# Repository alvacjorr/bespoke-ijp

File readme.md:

# bespoke-ijp

This repository is used for documents / code / notes related to the controller and software of the IEB bespoke inkjet printing rig. 
## Folder Structure
| Folder       |  Description  | 
| -------------| -------------|
| `/application`      | Code for the application/GUI |
| `/embedded`      | Code for the uSteppers |
| `/docs`      | Documentation |

## Workflow - Basics 
#### How do I get a copy of this repo?
- Install **Git**: https://help.github.com/en/github/getting-started-with-github/set-up-git
- Open up a terminal / command prompt and clone this repository: `git clone https://github.com/thekeeno/bespoke-ijp` which will give you a local copy of the main branch in the repository

#### Do I have to use a terminal?
- You can also use Git GUIs, e.g. https://desktop.github.com/ or https://www.gitkraken.com/

#### How do I keep my local copy updated?
- If you are on the main branch you can type `git pull`

#### How can I add / submit my changes?
- **The main main branch is protected, so you will have to create a separate branch and open a pull request.**
- The `main` branch should always reflect the newest agreed on version of the repository
- Make sure you branch off the latest state of main, i.e. on main type `git pull` or use `git fetch`
- To create a new branch use: `git checkout -b [branchname]`, e.g. `git checkout -b mg/new_branch`
- Make changes to files / add new files
- Take a look at the summary of changed files: `git status` 
- Add the new files to be tracked: `git add .` (to add all new files) or `git add code.m` (to add specific file)
- Commit the new changes (this creates a snapshot of repository state): `git commit -m "Change parameter gamma to 0.5"`
- Copy your new local branch with the new commits to the Github repository: `git push -u origin mg/new_branch`

- **Before your changes can be merged:** Make sure that you integrate the changes on `main` that others might have added in the meantime. This can be achieved by pulling the `main` changes to yout machine and then *merging* or preferably *rebasing* your commits onto the latest `main` version. See [here](https://gist.github.com/blackfalcon/8428401#keeping-current-with-the-master-branch) for a more detailed explanation.
- On https://github.com/oxfordcontrol/OxVentControl/ click on `Pull requests` -> `New Pull Request`. 
- Select `base:main` and `compare:mg/new_branch`
- All the changes can then be discussed in that pull request before they are approved and added to the main branch.
#### Useful git commands:
- https://rogerdudler.github.io/git-guide/
- https://confluence.atlassian.com/bitbucketserver/basic-git-commands-776639767.html
- http://ohshitgit.com/

## Workflow - Making Git collaboration easier 
A few steps everyone should take to make collaboration with Git easier:

#### Commit early and often
One commit should reflect one meaningful change to the code. Especially if we work on lots of different things at the same time, it is helpful if we create one meaningful commit for each significant change to the code. Notice that you don't have to commit all current changes at the same time. If you changed something in `A.cpp` and something different in `B.cpp`, you can do:
```bash
git add A.cpp
git commit -m "Fixed printing in A."
git add B.cpp
git commit -m "Changed parameters in B."
```
#### Combine temporary commits / clean up your history
If your recent 4 commits look like this `Fixed ABC`, `Work in progress`, `Working version` `Ups small fix` and you want to open a pull request to add this to the code you should first combine these commits into one commit. This can be done with an interactive  `git rebase`. To select the last 4 commits to squash, type:
```bash
git rebase -i HEAD~4
```
This should open an editor and show something like this:
```bash
pick d94e78 Fixed ABC     --- older commit
pick 4e9baa Work in progress
pick afb581 Working version  
pick 643d0e Ups small fix --- newer commit
```
Pick the oldest commit and squash the other ones into it by editing the file and saving it like this:
```bash
pick d94e78 Fixed ABC     --- older commit
s 4e9baa Work in progress
s afb581 Working version  
s 643d0e Ups small fix --- newer commit
```
You can then write a commit message for this combined commit. Combining commits can be very powerful, **but keep in mind that this rewrites the git history. Therefore never use the rebase on a remote branch where you know that other people rely on your history.**

[More info](https://www.internalpointers.com/post/squash-commits-into-one-git)

#### Write meaningful commit messages

Commit messages should make it easy to understand what particular change the commit implements. For more complex cases it can be helpful to write more than one sentence. To do that use the commit command without the message flag:
```bash
git commit
```
your default editor will open and you can write a longer form commit message. If you don't like the default editor you can set another one with:
```bash
git config --global core.editor "vim"
```

Follow the 7 rules of a great Git commit message

1. Separate subject from body with a blank line
2. Limit the subject line to 50 characters
3. Capitalize the subject line
4. Do not end the subject line with a period
5. Use the imperative mood in the subject line
6. Wrap the body at 72 characters
7. Use the body to explain what and why vs. how

[from here](https://chris.beams.io/posts/git-commit/)

#### Visualise the git tree before you merge
In order to not cause chaos with merges, it is helpful to take a look at the git commit tree and see where you currently are with your branch and where the branch you want to merge into currently is. You can either use a software package like [Gitkraken](https://www.gitkraken.com/) or alternatively use the command-line with:
```bash
git log --graph --decorate --oneline
```
If this is too long to remember you can create a Git Alias. On Unix systems type:
```bash
vim ~/.gitconfig
```
and add the line
```
[alias]
  gr = git log --graph --decorate --oneline
```
to the file.
#### Integrate the latest changes before opening a PR
If you are on the branch `my_fix` and want to open a PR to merge into `target_branch`, double-check if in the meantime any other changes happened on `target_branch` that might cause problems. To integrate the latest changes checkout the target branch:
```bash
git checkout target_branch
git pull origin target_branch
git checkout my_fix
```
To integrate the changes you can either `rebase` or `merge`. Rebasing is the cleaner way of the two as it doesn't introduce new merge commits. It essentially replays all of your new commits in `my_fix` onto the latest commit of `target_branch`. In some cases this will not go smoothly and you'll have to fix the conflicts as the commits are applied. **Again note that the rebase will rewrite history, so only do that if you know nobody else relies on the commits that will be rewritten**.

[Merging vs. Rebasing](https://www.atlassian.com/git/tutorials/merging-vs-rebasing)

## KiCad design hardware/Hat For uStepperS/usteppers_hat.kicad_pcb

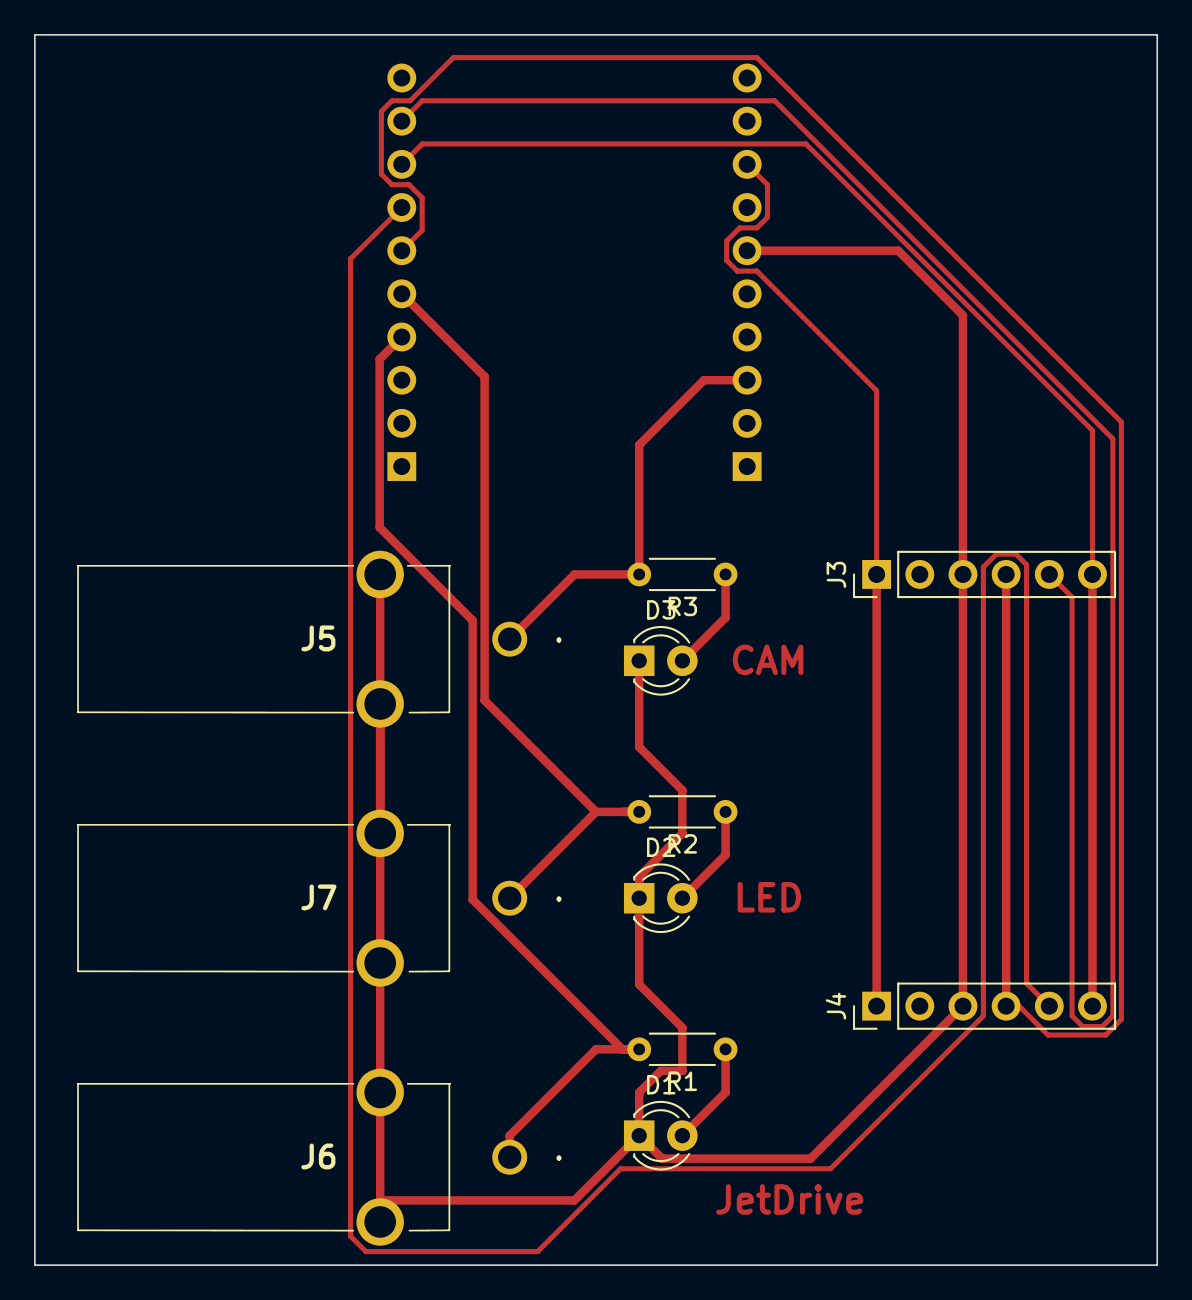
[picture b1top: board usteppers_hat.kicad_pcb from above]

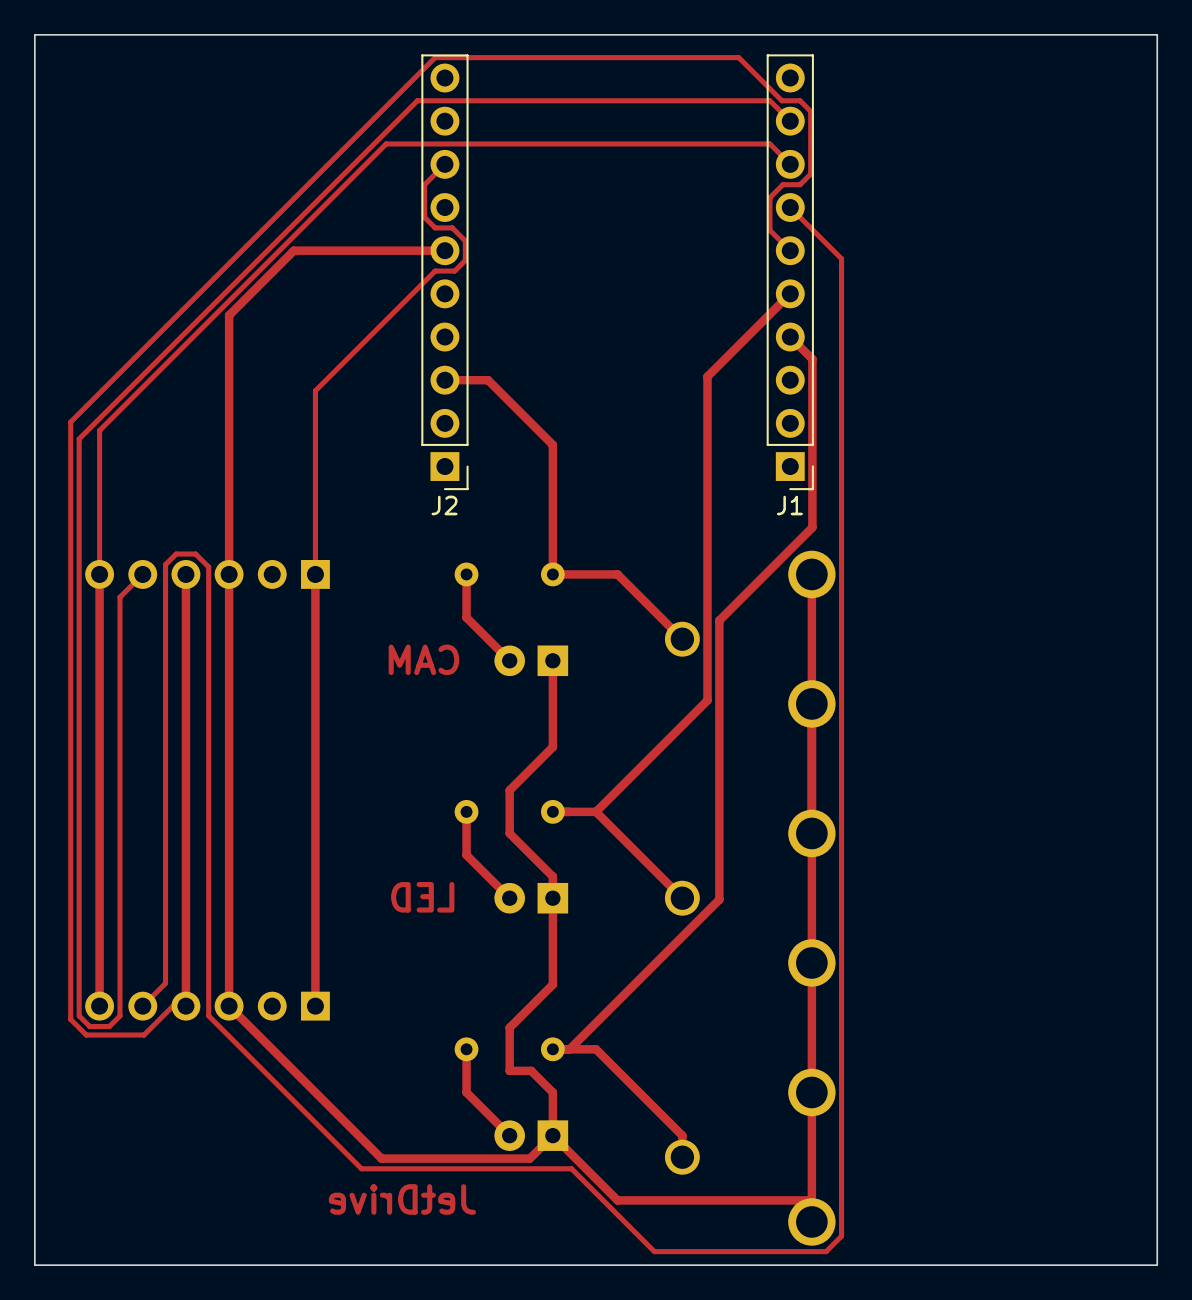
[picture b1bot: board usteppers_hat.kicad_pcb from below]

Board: 2 copper layers, 66.0 x 72.4 mm, 13 parts (2 on the bottom side), 13 nets.

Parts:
D1, D2, D3: LED; LED_D3.0mm
J1, J2: Conn_01x10_Male; PinHeader_1x10_P2.54mm_Vertical
J3, J4: Conn_01x06_Female; PinHeader_1x06_P2.54mm_Vertical
J5, J6, J7: 5414373-1; 54143731
R1, R2, R3: 330; R_Axial_DIN0204_L3.6mm_D1.6mm_P5.08mm_Horizontal

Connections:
/5V: J2.8, J3.1, J4.1
/A0: J2.3, J5.1, R3.2
/CLK: J1.8, J3.6, J4.6
/CS1: J1.7, J4.5
/CS2: J1.9, J3.5
/D3: J1.4, J6.1, R1.2
/D4: J1.5, J7.1, R2.2
/D5: J1.6, J3.4, J4.4
/VIN: J2.4, J2.5
Earth: D1.1, D2.1, D3.1, J1.10, J2.6, J2.7, J3.3, J4.3, J5.2, J5.3, J6.2, J6.3, J7.2, J7.3
unnamed: D1.2, R1.1
unnamed: D2.2, R2.1
unnamed: D3.2, R3.1

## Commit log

2021-01-29 First commit.
2021-01-29 add readme
2021-02-04 add documentation
2021-02-04 add a gitignore
2021-02-11 add util to list attached serial devices
2021-02-11 add PSU tracking functions - minor issue with error messages though.
2021-02-12 add temperature readout, fix issue with polling PSU
2021-02-12 add temperature graphs
2021-02-12 remove temperature printing
2021-02-13 add docs badge to readme.md
2021-02-13 gitignore docs build
2021-02-13 add introduction to docs
2021-02-13 beginning of documentation
2021-02-13 remove pythonpath from conf.py
2021-02-13 fix toctree
2021-02-13 more docs
2021-02-13 first attempt to add docstrings
2021-02-13 more documentation added inc poweron procedure
2021-02-13 even more docs, including some build instructions and poweron procedure
2021-02-13 alteration to gitignore to ignore local builds of html docs
2021-02-13 fix html links
2021-02-13 split docs across separate files
2021-02-13 add background documentation
2021-02-13 tidy ToC
2021-02-13 change theme
2021-02-13 add more docstrings to code
2021-02-13 remove autodoc
2021-02-13 gitignore update
2021-02-13 fix conf.py
2021-02-13 add autodoc
2021-02-13 more docstrings in the code
2021-02-14 more docstrings
2021-02-14 add docs section for known issues
2021-02-14 add issues page to index
2021-02-14 more building instructions
2021-02-16 change master to main in readme.md
2021-02-16 warp scripts in init main conditional
2021-02-16 expand issues
2021-02-16 more thermocouple work
2021-02-19 split modules into separate files
2021-02-19 temp fix for PSU issue, rearrange UI
2021-02-19 move autodoc to separate folder
2021-02-19 blue graph
2021-02-19 tuning pid
2021-02-23 generalise PID controller to separate windows
2021-02-23 add backlash issue
2021-02-23 add comments about AFGs
2021-02-24 add basic libraries for AFG
2021-03-01 update afg class
2021-03-01 update logs
2021-03-01 add thorlabs half inch mirror
2021-03-08 made a holder for microscope slides
2021-03-08 made a half inch thorlabs mirror holder
2021-03-08 fillet and label crude slide holder
2021-03-08 create perpendicular stage holder
2021-03-08 add older CAD designs, rearrange hardware folder
2021-03-11 add more 3dp optical parts
2021-03-11 add A and B triggers on pins 2 and 3 to uStepper firmware
2021-03-15 add A and B triggers using software delay
2021-03-15 add phlatlight parts
2021-03-17 add microfab nozzle schematic (inches)
2021-03-17 add placeholder element for photofluor head
2021-03-23 add optical parts
2021-03-23 add trigger software
2021-03-23 add example image for chopper
2021-03-24 add TIMER3 based single-shot trigger
2021-03-24 add timer3 based dual trigger
2021-03-24 separate out trigger fn
2021-03-31 add UI control of trigger timing
2021-03-31 move trigger to D7 and D8 (PORTE1, PORTE0)
2021-03-31 add PCINT2 interrupt and move trig out to 7, 8
2021-03-31 clarify workings of PCINT interrupts
2021-03-31 add double-flash feature
2021-03-31 change popup windows to be of Qt.Tool type
2021-03-31 allow for negative values in mm and angle spinboxes
2021-03-31 first draft of progressive print mode
2021-04-08 add autoconfiguration of x and y axes
2021-04-08 add better docs to the port config utility
2021-04-15 add triple trigger system
2021-04-15 more triple trigger
2021-04-15 add toggle switch for second LED pulse
2021-04-15 embedded code for second LED pulse
2021-04-15 add simple progressive mode on primary axis
2021-04-15 tweak to last commit
2021-04-15 increase radius of angled nozzle holder
2021-04-15 replace external thread w/ internal thread #10
2021-04-15 update gitignore to ignore solidworks temp files #11
2021-04-15 alter phlatlight base to mount onto an optical table
2021-04-15 add sketch of photofluor holder
2021-04-15 make gitignore ignore SLDDRW temp files
2021-04-15 documentation update to reflect auto-selection of com ports
2021-04-15 fix prog mode overshoot on enable
2021-04-25 improve failover for when no stage attached
2021-04-25 tweak for pylint
2021-04-27 clarify definitions of trigger out pins
2021-04-28 add FPS cap to progressive trigger
2021-04-28 add continuous mode
2021-04-28 add library for photofluor
2021-04-29 add comments to clarify how adding settings works
2021-05-13 add error message for failed PSU data grab
2021-06-04 add sita tensiometer library
2021-06-06 add drawings of perpendicular stage holder
2021-06-06 add various drawings and assemblies
2021-06-06 add open loop option (as default) to angle movement
2021-06-08 change drop, led and camera trigger outputs to D3, D4 and A0 respectively
2021-06-08 change default FPS to 20
2021-06-08 intergrate digital temperature control with ustepper code
2021-06-08 tidy up after degital temp work
2021-06-11 tweak PID and enable PoM mode
2021-06-11 add comments on thermocouple grounding
2021-06-15 add further comments on thermocouple
2021-06-15 demo of docs
2021-06-16 add 3d models of motor offset and new phlatlight holder
2021-06-16 add notes on camera software
2021-06-25 Add block diagrams
2021-06-30 alter phlatlight holder to better fit table
2021-07-02 thin out holes in motor offset
2021-07-02 create new complex slide holder system
2021-07-04 add full assembly of xy stage and other CAD parts
2021-07-05 minor tweaks to pf and nozzle holder
2021-07-05 further corrections to pf-nozzle holder
2021-07-05 minor tweak to hole separation in pf and nozzle holder
2021-07-05 change heater mount holes to threads
2021-07-05 add new small printhead
2021-07-05 move old EP designs
2021-07-05 add engineering drawing of new small printhead
2021-07-06 add optional redirection of stderr and stdout to main window
2021-07-07 improve user guide especially re IC Capture
2021-07-07 more documentation
2021-07-07 tweaks to slide holder assembly based on feedback from first print
2021-07-07 further tweaks to complex slide holder
2021-07-21 add laser cut offset parts
2021-07-21 add thicker optical adapter
2021-07-21 add photofluor controller support
2021-07-23 rework most CAD files, add vertical stage
2021-08-17 add substantial hardware revisions
2021-08-26 more hardware work
2021-09-08 add new heated slide holder
2021-10-05 add 3d printed ITO etching templaets
2021-10-05 add thorlabs icroscope holder
2021-10-06 retune and improve PID for new heat element
2021-10-06 remove printing of deltas on some motion funcs
2021-10-06 add grid-printing macro with backlash comp
2021-10-07 QOL improvements to heater control
2021-10-08 switch power supply off on exit
2021-10-08 add comments
2021-10-08 ignore some testing files
2021-11-04 QOL improvements to heater control and swap to CH3
2021-12-13 better exception handling for stepper connection
2021-12-13 add burst mode
2022-04-08 add configurable maximum number of grid items
2022-04-08 preliminary grid class work
2023-05-30 name changes
2024-11-05 add spectra from light source
2024-11-05 hardware updates for thesis
